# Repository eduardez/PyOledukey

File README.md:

# PyOledUkey

Custom ortholinear keyboard with OLED display and two rotatory encoders.

TO DO: Documentation

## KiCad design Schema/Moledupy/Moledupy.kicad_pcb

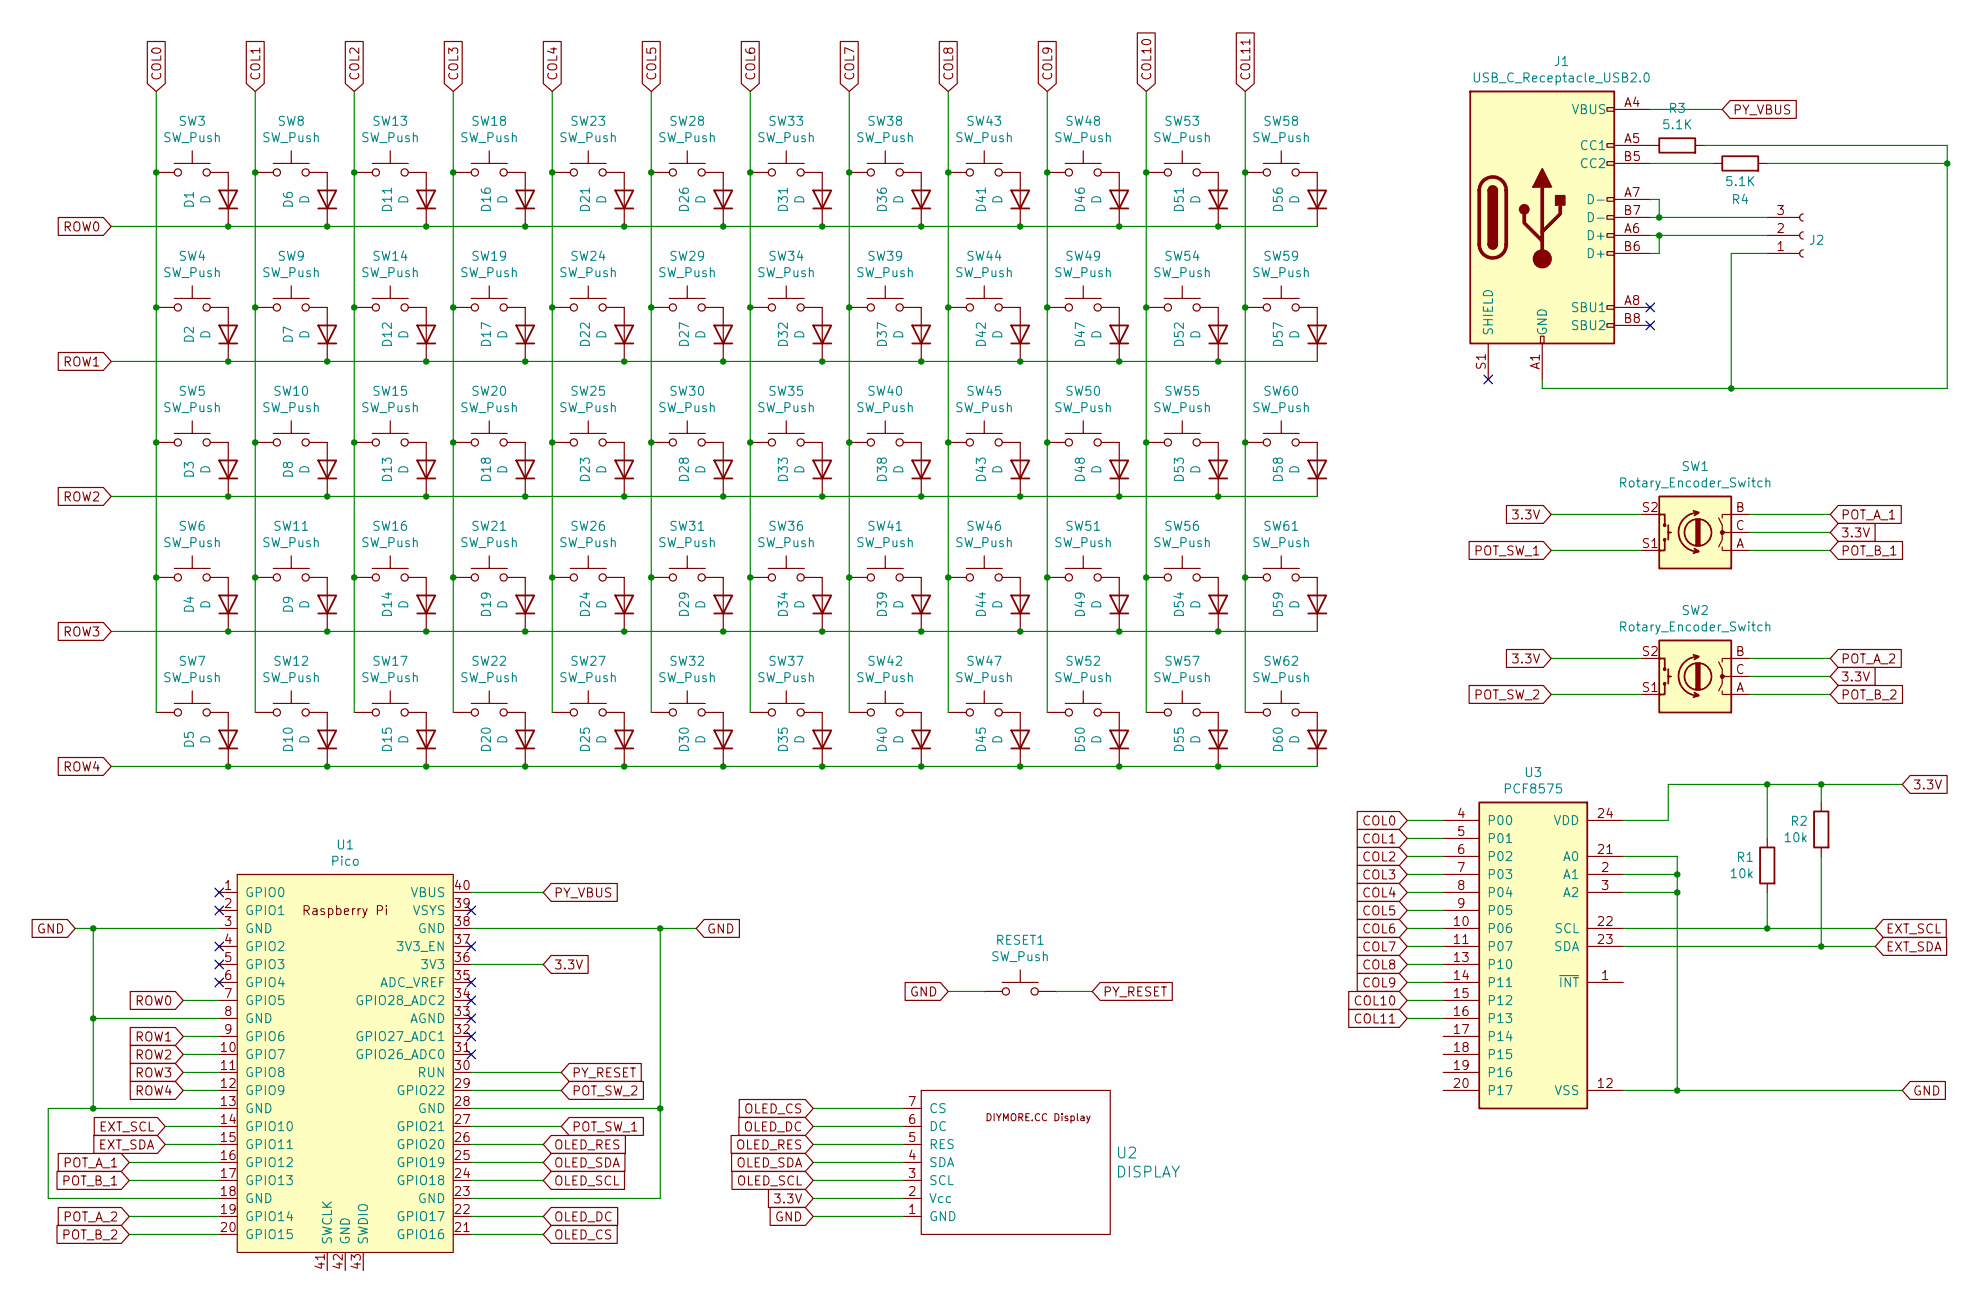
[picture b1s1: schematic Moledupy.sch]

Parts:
D1, D2, D3, D4, D5, D6, D7, D8, D9, D10, D11, D12, D13, D14, D15, D16, D17, D18, D19, D20, D21, D22, D23, D24, D25, D26, D27, D28, D29, D30, D31, D32, D33, D34, D35, D36, D37, D38, D39, D40, D41, D42, D43, D44, D45, D46, D47, D48, D49, D50, D51, D52, D53, D54, D55, D56, D57, D58, D59, D60: D; D_0603_1608Metric
J1: USB_C_Receptacle_USB2.0; USB_C_Receptacle_XKB_U262-16XN-4BVC11
J2: PinSocket_1x03_P2.00mm_Vertical
R1, R2: 10k; R_Axial_DIN0207_L6.3mm_D2.5mm_P10.16mm_Horizontal
R3, R4: 5.1K; R_Axial_DIN0207_L6.3mm_D2.5mm_P10.16mm_Horizontal
RESET1: SW_Push; SW_PUSH_6mm_H5mm
SW1, SW2: Rotary_Encoder_Switch; RotaryEncoder_Alps_EC11E-Switch_Vertical_H20mm
SW3, SW4, SW5, SW6, SW7, SW8, SW9, SW10, SW11, SW12, SW13, SW14, SW15, SW16, SW17, SW18, SW19, SW20, SW21, SW22, SW23, SW24, SW25, SW26, SW27, SW28, SW29, SW30, SW31, SW33, SW34, SW35, SW36, SW38, SW39, SW40, SW41, SW42, SW43, SW44, SW45, SW46, SW47, SW48, SW49, SW50, SW51, SW52, SW53, SW54, SW55, SW56, SW57, SW58, SW59, SW60, SW61, SW62: SW_Push; SW_Cherry_MX_1.00u_PCB
SW32, SW37: SW_Push; SW_Cherry_MX_2.25u_PCB
U1: Pico; RPi_Pico_SMD_TH
U2: DISPLAY; Adafruit_SSD1306_No_Mounting_Holes
U3: PCF8575; PCF8575TS; MPN PCF8575TS/1,112

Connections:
3.3V: R1.1, R2.1, SW1.C, SW1.S2, SW2.C, SW2.S2, U1.36 (3V3), U2.2 (Vcc), U3.24 (VDD)
COL0: SW3.1, SW4.1, SW5.1, SW6.1, SW7.1, U3.4 (P00)
COL1: SW8.1, SW9.1, SW10.1, SW11.1, SW12.1, U3.5 (P01)
COL2: SW13.1, SW14.1, SW15.1, SW16.1, SW17.1, U3.6 (P02)
COL3: SW18.1, SW19.1, SW20.1, SW21.1, SW22.1, U3.7 (P03)
COL4: SW23.1, SW24.1, SW25.1, SW26.1, SW27.1, U3.8 (P04)
COL5: SW28.1, SW29.1, SW30.1, SW31.1, SW32.1, U3.9 (P05)
COL6: SW33.1, SW34.1, SW35.1, SW36.1, SW37.1, U3.10 (P06)
COL7: SW38.1, SW39.1, SW40.1, SW41.1, SW42.1, U3.11 (P07)
COL8: SW43.1, SW44.1, SW45.1, SW46.1, SW47.1, U3.13 (P10)
COL9: SW48.1, SW49.1, SW50.1, SW51.1, SW52.1, U3.14 (P11)
COL10: SW53.1, SW54.1, SW55.1, SW56.1, SW57.1, U3.15 (P12)
COL11: SW58.1, SW59.1, SW60.1, SW61.1, SW62.1, U3.16 (P13)
EXT_SCL: R1.2, U1.14 (GPIO10), U3.22 (SCL)
EXT_SDA: R2.2, U1.15 (GPIO11), U3.23 (SDA)
GND: RESET1.1, U1.3 (GND), U1.8 (GND), U1.13 (GND), U1.18 (GND), U1.23 (GND), U1.28 (GND), U1.38 (GND), U2.1 (GND), U3.2 (A1), U3.3 (A2), U3.12 (VSS), U3.21 (A0)
unnamed: D1.2 (A), SW3.2
unnamed: D2.2 (A), SW4.2
unnamed: D3.2 (A), SW5.2
unnamed: D4.2 (A), SW6.2
unnamed: D5.2 (A), SW7.2
unnamed: D6.2 (A), SW8.2
unnamed: D7.2 (A), SW9.2
unnamed: D8.2 (A), SW10.2
unnamed: D9.2 (A), SW11.2
unnamed: D10.2 (A), SW12.2
unnamed: D11.2 (A), SW13.2
unnamed: D12.2 (A), SW14.2
unnamed: D13.2 (A), SW15.2
unnamed: D14.2 (A), SW16.2
unnamed: D15.2 (A), SW17.2
unnamed: D16.2 (A), SW18.2
unnamed: D17.2 (A), SW19.2
unnamed: D18.2 (A), SW20.2
unnamed: D19.2 (A), SW21.2
unnamed: D20.2 (A), SW22.2
unnamed: D21.2 (A), SW23.2
unnamed: D22.2 (A), SW24.2
unnamed: D23.2 (A), SW25.2
unnamed: D24.2 (A), SW26.2
unnamed: D25.2 (A), SW27.2
unnamed: D26.2 (A), SW28.2
unnamed: D27.2 (A), SW29.2
unnamed: D28.2 (A), SW30.2
unnamed: D29.2 (A), SW31.2
unnamed: D30.2 (A), SW32.2
unnamed: D31.2 (A), SW33.2
unnamed: D32.2 (A), SW34.2
unnamed: D33.2 (A), SW35.2
unnamed: D34.2 (A), SW36.2
unnamed: D35.2 (A), SW37.2
unnamed: D36.2 (A), SW38.2
unnamed: D37.2 (A), SW39.2
unnamed: D38.2 (A), SW40.2
unnamed: D39.2 (A), SW41.2
unnamed: D40.2 (A), SW42.2
unnamed: D41.2 (A), SW43.2
unnamed: D42.2 (A), SW44.2
unnamed: D43.2 (A), SW45.2
unnamed: D44.2 (A), SW46.2
unnamed: D45.2 (A), SW47.2
unnamed: D46.2 (A), SW48.2
unnamed: D47.2 (A), SW49.2
unnamed: D48.2 (A), SW50.2
unnamed: D49.2 (A), SW51.2
unnamed: D50.2 (A), SW52.2
unnamed: D51.2 (A), SW53.2
unnamed: D52.2 (A), SW54.2
unnamed: D53.2 (A), SW55.2
unnamed: D54.2 (A), SW56.2
unnamed: D55.2 (A), SW57.2
unnamed: D56.2 (A), SW58.2
unnamed: D57.2 (A), SW59.2
unnamed: D58.2 (A), SW60.2
unnamed: D59.2 (A), SW61.2
unnamed: D60.2 (A), SW62.2
unnamed: J1.A1 (GND), J1.A12 (GND), J1.B1 (GND), J1.B12 (GND), J2.1, R3.2, R4.2
unnamed: J1.A5 (CC1), R3.1
unnamed: J1.A6 (D+), J1.B6 (D+), J2.2
unnamed: J1.A7 (D-), J1.B7 (D-), J2.3
unnamed: J1.B5 (CC2), R4.1
OLED_CS: U1.21 (GPIO16), U2.7 (CS)
OLED_DC: U1.22 (GPIO17), U2.6 (DC)
OLED_RES: U1.26 (GPIO20), U2.5 (RES)
OLED_SCL: U1.24 (GPIO18), U2.3 (SCL)
OLED_SDA: U1.25 (GPIO19), U2.4 (SDA)
POT_A_1: SW1.B, U1.16 (GPIO12)
POT_A_2: SW2.B, U1.19 (GPIO14)
POT_B_1: SW1.A, U1.17 (GPIO13)
POT_B_2: SW2.A, U1.20 (GPIO15)
POT_SW_1: SW1.S1, U1.27 (GPIO21)
POT_SW_2: SW2.S1, U1.29 (GPIO22)
PY_RESET: RESET1.2, U1.30 (RUN)
PY_VBUS: J1.A4 (VBUS), J1.A9 (VBUS), J1.B4 (VBUS), J1.B9 (VBUS), U1.40 (VBUS)
ROW0: D1.1 (K), D6.1 (K), D11.1 (K), D16.1 (K), D21.1 (K), D26.1 (K), D31.1 (K), D36.1 (K), D41.1 (K), D46.1 (K), D51.1 (K), D56.1 (K), U1.7 (GPIO5)
ROW1: D2.1 (K), D7.1 (K), D12.1 (K), D17.1 (K), D22.1 (K), D27.1 (K), D32.1 (K), D37.1 (K), D42.1 (K), D47.1 (K), D52.1 (K), D57.1 (K), U1.9 (GPIO6)
ROW2: D3.1 (K), D8.1 (K), D13.1 (K), D18.1 (K), D23.1 (K), D28.1 (K), D33.1 (K), D38.1 (K), D43.1 (K), D48.1 (K), D53.1 (K), D58.1 (K), U1.10 (GPIO7)
ROW3: D4.1 (K), D9.1 (K), D14.1 (K), D19.1 (K), D24.1 (K), D29.1 (K), D34.1 (K), D39.1 (K), D44.1 (K), D49.1 (K), D54.1 (K), D59.1 (K), U1.11 (GPIO8)
ROW4: D5.1 (K), D10.1 (K), D15.1 (K), D20.1 (K), D25.1 (K), D30.1 (K), D35.1 (K), D40.1 (K), D45.1 (K), D50.1 (K), D55.1 (K), D60.1 (K), U1.12 (GPIO9)

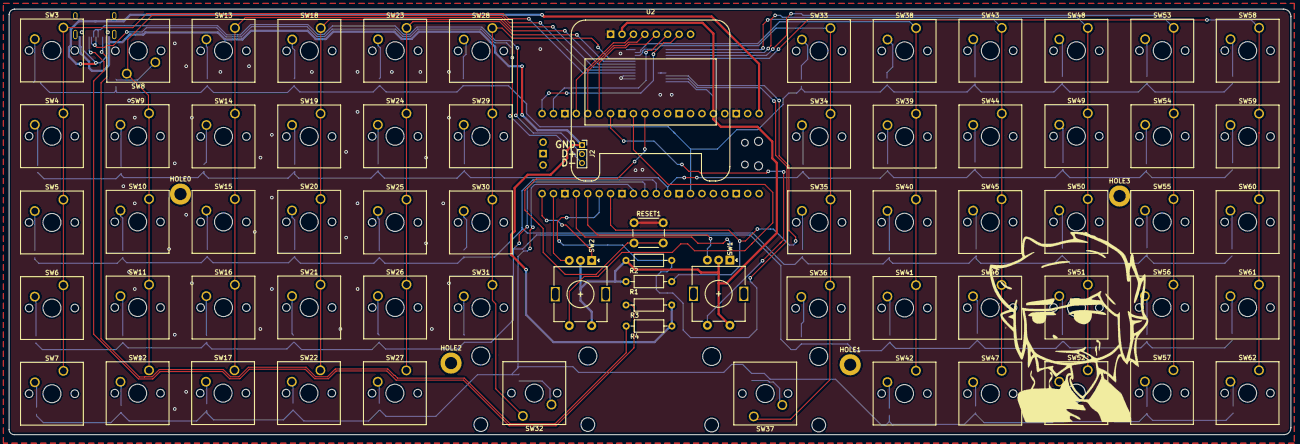
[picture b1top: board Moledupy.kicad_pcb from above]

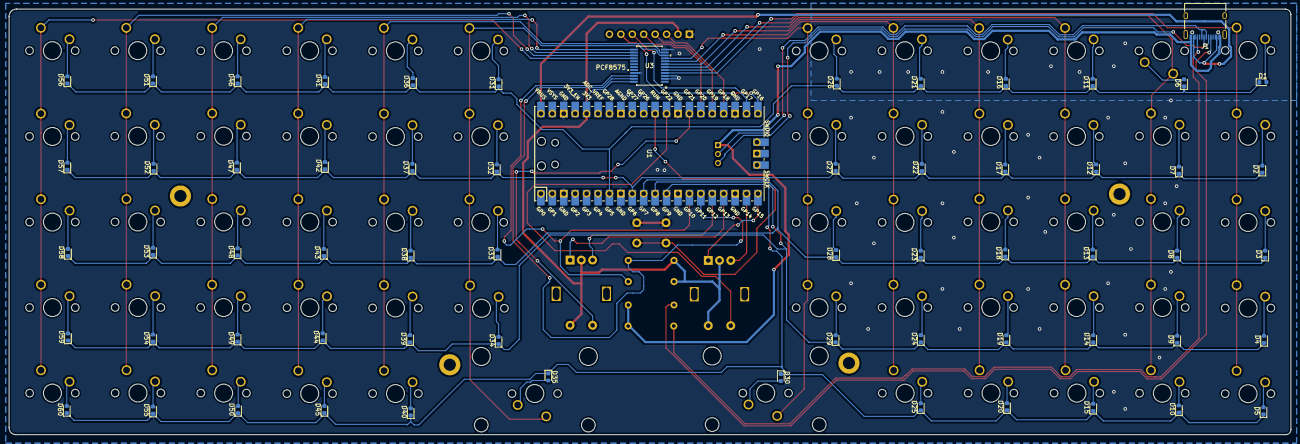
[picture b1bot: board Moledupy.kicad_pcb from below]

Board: 2 copper layers, 285.0 x 94.6 mm, 136 parts (63 on the bottom side), 99 nets.

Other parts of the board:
HOLE0, HOLE1, HOLE2, HOLE3: MountingHole_2.7mm_M2.5_DIN965_Pad

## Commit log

2022-08-16 True initial commit
2022-10-09 Commit Inicial
2022-10-09 Added readme

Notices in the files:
parts and their libraries:
Copyright 2021 Accelerated Designs. All rights reserved.
